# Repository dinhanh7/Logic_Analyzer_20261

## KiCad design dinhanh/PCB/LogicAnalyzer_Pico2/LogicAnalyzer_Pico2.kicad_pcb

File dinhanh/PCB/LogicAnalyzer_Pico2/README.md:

# PCB đế Pico 2 — Logic Analyzer 8 kênh, Layout A

**Rev A1 — 11/11/2026. Bản thiết kế để nhóm duyệt, chưa phát hành sản xuất.**

Đã vẽ schematic và PCB 2 lớp **160 × 110 mm**, đi dây, đổ đồng GND, bố trí 4 lỗ M3. Pico 2 đã hàn chân đực cắm vào **hai socket cái 1×20, bước 2,54 mm**, khoảng cách hai hàng **17,78 mm**. USB trên Pico quay ra mép trên; dùng USB này để cấp nguồn và giao tiếp PC.

Căn cứ: [spec](../SPEC_PCB.md), [phản hồi Nam Khánh](../REPLY_SPEC_PCB.md), [mạch bảo vệ LTspice](../../mach_bao_ve/ltspice/README.md). Không thay đổi source firmware hoặc file mô phỏng trong lần vẽ PCB này.

## Mở và duyệt

- Mở **[LogicAnalyzer_Pico2.kicad_pro](LogicAnalyzer_Pico2.kicad_pro)** trong KiCad 10, rồi mở Schematic Editor / PCB Editor.
- Schematic native: [LogicAnalyzer_Pico2.kicad_sch](LogicAnalyzer_Pico2.kicad_sch); PCB native: [LogicAnalyzer_Pico2.kicad_pcb](LogicAnalyzer_Pico2.kicad_pcb).
- [Schematic PDF](review/Schematic.pdf), [ảnh 3D mặt trên](review/PCB_3D_top.png), [ảnh 3D phối cảnh](review/PCB_3D_isometric.png).
- [Mặt trên SVG](review/PCB_top.svg), [mặt dưới SVG](review/PCB_bottom.svg), [bản đồ lắp linh kiện](review/Assembly.svg).
- [PDF mặt trên tỉ lệ 1:1](review/PCB_top_1to1.pdf), [PDF mặt dưới tỉ lệ 1:1](review/PCB_bottom_1to1.pdf): in **Actual size / 100%**, kiểm tra bằng thước trước khi đối chiếu socket.
- [BOM từng vị trí](BOM.csv), [BOM gộp và phần mua ngoài bo](BOM_grouped.csv).
- [Gerber + drill để duyệt](fabrication_review/). Các file này chưa được nhóm xác nhận để đặt làm bo.

Symbol, footprint và model cần dùng được kèm trong project bằng đường dẫn `${KIPRJMOD}`. Không cần thư viện riêng đã bị xóa ở `mach_bao_ve/kicad/`. Xem [nguồn thư viện](LIBRARY_SOURCES.md). Model PR02 là hình minh họa theo kích thước danh định; model Pico đi kèm thư viện KiCad minh họa cơ khí dòng Pico, không thể hiện chính xác linh kiện RP2350 trên Pico 2. Chưa dựng model TFT/hộp vì chưa có mã module và cơ khí thực tế.

## Chức năng và kết nối

### Tám kênh bảo vệ

Mỗi kênh có đường tín hiệu:

```text
J1 CHn → 1k PR02 → 1k PR02 → CLAMP_n → 330Ω → A_n → SN74LVC1G17 → 33Ω → GPn
                                                       │
                                                      47k
                                                       │
                                                      GND

BAV99: pin 1 = GND; pin 2 = Z_n; pin 3 = CLAMP_n
BZX85C3V3: cathode = Z_n; anode = GND
```

Tổng cộng **16 điện trở PR02 Cu-lead 1 kΩ/2 W**. Mã đề xuất theo cấu trúc mã Vishay là **PR02000201001FA100** (1%); cần đối chiếu mã đặt mua thực tế, không thay bằng PR02 FeCu công suất khác hoặc điện trở SMD thông thường. Footprint riêng: thân tối đa 10 × Ø3,9 mm, khoảng cách chân 17,78 mm, lỗ khoan 1,2 mm. Chừa khoảng trống giữa các thân điện trở; các điện trở/tụ tín hiệu còn lại dùng 0805 để dễ hàn tay, tụ khối dùng 1206.

**Z_n là nút kẹp riêng từng kênh, không nối rail 3V3.** Chỉ ngõ Y của buffer qua điện trở 33 Ω tới Pico. Test point gồm OUT0…OUT7, 3V3, VSYS, GND; CH0 có thêm IN/CLAMP/A/Z. TP là pad đồng trên bo, không phải linh kiện phải mua.

Đồng GND mặt dưới nằm từ x = 65 mm sang vùng bảo vệ/Pico/giao diện; không trải dưới phần lớn vùng điện trở đầu vào. Có đường GND riêng rộng 0,8 mm vòng dưới vùng điện trở nối về đầu probe. Đây là thiết bị **chung GND với DUT/PC**, không cách ly.

### Đầu nối

| Đầu nối | Pin | Chức năng |
|---|---|---|
| J1 — 2×8 | 1,3,5,7,9,11,13,15 | CH0…CH7 |
| J1 — 2×8 | 2,4,6,8,10,12,14,16 | GND |
| J2 — 1×8 | 1 / 2 | GND / 3V3 |
| J2 | 3 / 4 | TFT SCK GP10 / MOSI GP11 |
| J2 | 5 / 6 | TFT RST GP15 / DC GP14 |
| J2 | 7 / 8 | TFT CS GP13 / BL sau tầng lái GP16 |
| J3 — 1×2 | 1 / 2 | CAL_OUT GP27 / GND |

**J2 là đầu cáp được gán tín hiệu rõ ràng, chưa phải đầu cắm trực tiếp tương thích mọi module ST7735.** Phải nối dây theo nhãn của module thật. Chưa đặt lỗ bắt vít cố định cho TFT; dùng gá/hộp riêng sau khi đo module.

### Nút, LED, nguồn

| Vị trí | Chức năng | Pico |
|---|---|---|
| SW1 / SW2 | UP / DOWN, nhấn nối GND | GP8 / GP9 |
| SW3 / SW4 | OK / BACK, nhấn nối GND | GP12 / GP22 |
| SW5 | RESET, nhấn nối GND | RUN |
| D17 | PWR từ 3V3 qua 1 kΩ | — |
| D18 | STATUS qua 1 kΩ, HIGH sáng | GP26 |
| J3 | Xung tự kiểm tra 3,3 V | GP27 |

Các nút chức năng dùng pull-up nội và debounce firmware; RUN đã có pull-up trên module. GP17…GP21 và GP28 để trống. CAL_OUT không nối sẵn vào đầu đo; nối bằng dây khi kiểm tra và không dùng để cấp nguồn DUT.

Nguồn duy nhất là USB trên Pico; rail 3V3 từ pin 36 cấp buffer, TFT, BL và LED. VSYS chỉ đưa ra TP10. Có C9/C10 10 µF/10 V và 100 nF cạnh mỗi buffer. Chưa đo tổng dòng; yêu cầu tải ngoài nằm trong ngân sách nguồn Pico, mục tiêu dưới 300 mA. Kiểm tra dòng module TFT, BL và sụt áp thực tế trước khi duyệt.

### Tầng lái BL bổ sung

Q1 BC817-40 và Q2 BC807-40 tạo công tắc cấp 3,3 V cho BL, **GP16 HIGH → sáng**, giữ logic Layout A. GPIO chỉ cấp dòng base khoảng 0,5 mA, không trực tiếp cấp dòng LED nền. Có điện trở kéo để BL tắt khi GPIO ở trạng thái thả nổi.

R47 mặc định **100 Ω, 0805, chọn công suất ≥0,25 W** để giới hạn dòng tối đa lý thuyết 33 mA nếu đầu BL chập GND. Với module có điện trở hoặc mạch BL riêng, độ sáng có thể thấp. Chỉ thay trị số sau khi biết cấu trúc BL và dòng thực tế; không tự lắp 0 Ω trước khi kiểm tra. Tầng này dùng với đầu BL nhận mức/dòng dương 3,3 V; nếu module có BL kiểu khác phải sửa trước khi cắm.

## Kết quả kiểm tra bản vẽ

KiCad **10.0.8**:

| Kiểm tra | Kết quả |
|---|---:|
| [ERC schematic](review/ERC.json) | 0 lỗi, 0 cảnh báo |
| [DRC PCB, gồm đối chiếu schematic](review/DRC.json) | 0 vi phạm |
| Kết nối PCB còn thiếu | 0 |
| Sai khác PCB với schematic | 0 |
| [Kiểm tra topology/pinout riêng](review/connectivity_check.json) | 84 kiểm tra đạt |

Không thêm ngoại lệ DRC để bỏ qua lỗi. Quy tắc bo: clearance tín hiệu mặc định 0,22 mm; net trước hai điện trở đầu vào 0,75 mm; rộng dây nhỏ nhất 0,20 mm, danh định 0,25 mm; via tối thiểu 0,60/0,30 mm; cách mép đồng 0,50 mm. Các trị số này là lựa chọn layout prototype, không phải chứng nhận cách điện hay mức đo CAT.

Đã dùng đường đi ngắn trong từng front-end; dây buffer→Pico có chiều dài khác nhau, chưa cân bằng timing bằng đo thực nghiệm. Kiểm tra 84 điều kiện dùng netlist xuất thật để xác nhận pin probe, hai điện trở nối tiếp, các nút Z riêng, mapping Layout A và việc không nối nút trước buffer vào chân capture.

Đi dây phần còn lại bằng **Freerouting 2.5.0 chạy cục bộ**, sau đó sửa copper bằng KiCad và kiểm tra lại DRC. Không gửi thiết kế lên dịch vụ route đám mây. File DSN/SES được giữ trong `review/` để truy vết; **PCB native hiện tại đã có chỉnh sửa sau SES**, nên không import lại SES lên bản này.

## Những điểm cần nhóm chốt trước khi đặt làm

1. **Đối chiếu Pico/socket thật:** in PDF 1:1, thử khoảng cách chân và chiều cắm, chiều cao socket, USB/BOOTSEL/SWD. Không cắm ngược Pico. Lỗ H1…H4 là Ø3,2 mm tại (4;4), (156;4), (4;106), (156;106) mm, tính từ góc trên trái.
2. **Module TFT thật:** thứ tự chân, nguồn 3,3 V, cấu trúc/dòng BL, dây nối J2 và chỗ gá màn hình. Không cấp 5 V lên J2.
3. **Linh kiện bảo vệ:** xác nhận mã PR02 Cu, đường cong chịu xung/điện áp, mã BAV99/BZX85C3V3/SN74LVC1G17DBVR và package. Kiểm tra điện áp chịu được của đầu nối/dây probe được mua. Trị số 2×1 kΩ trên PCB khớp tổng R=2 kΩ của mô hình cũ, nhưng hồ sơ LTspice vẫn cần cập nhật thành hai linh kiện và xét dung sai/ký sinh.
4. **Điện và timing:** kiểm thử 0/3,3 V trước, mapping từng kênh, dòng nguồn, TFT/nút/BL; đánh giá +12 V DC và mô phỏng xung +200 V/1 ms với linh kiện thực tế; xác minh dải 1 kHz–1 MHz và lệch thời gian giữa kênh. **25 MS/s không có nghĩa băng thông đầu vào 25 MHz. ERC/DRC không chứng minh chịu quá áp.**
5. **Cơ khí và chi phí:** duyệt kích thước 160×110 mm, cách gá TFT/hộp, báo giá PCB/linh kiện và mục tiêu ≤450.000 đ. Chưa có báo giá để xác nhận đạt ngân sách.

## Script và tái tạo

Các script nằm trong `scripts/`; đây là công cụ tạo bản ban đầu, **chạy lại có thể ghi đè sửa tay**. Hai file native hiện tại là kết quả bàn giao chính.

Thứ tự dựng lại: `generate_schematic.py` (Python có `sexpdata`) → KiCad CLI xuất `review/netlist.xml` → `generate_board.py` (Python có `pcbnew`) → Freerouting xuất `review/routed.ses` → `finish_board.py` → `refine_board.py` → `add_preview_models.py` → chạy lại ERC/DRC và `verify_connectivity.py`. Phải xuất lại PDF/Gerber sau mỗi thay đổi.

`generate_board.py` tạo phần bố trí và dây cục bộ, không tự tái tạo phần route từ Freerouting. KiCad đang cài qua AppDir có thể chạy các script PCB bằng `AppRun python3.11 <script>`. Các file native mở bằng KiCad không cần Python hay Freerouting.

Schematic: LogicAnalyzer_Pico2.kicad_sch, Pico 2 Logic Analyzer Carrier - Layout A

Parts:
C1, C2, C3, C4, C5, C6, C7, C8: 100n 10V; C0805
C9, C10: 10u / 10V X7R; C1206
D1, D3, D5, D7, D9, D11, D13, D15: BAV99; SOT23
D2, D4, D6, D8, D10, D12, D14, D16: BZX85C3V3; Zener_DO41
D17: PWR; LED0805
D18: STATUS; LED0805
H1, H2, H3, H4: M3 / 3.2mm; Hole_M3
J1: PROBE CH0..7 / GND; Probe_2x08
J2: TFT CABLE / 3V3 ONLY; TFT_1x08
J3: CAL OUT / GND; CAL_1x02
Q1: BC817-40; SOT23
Q2: BC807-40; SOT23
R1, R2, R6, R7, R11, R12, R16, R17, R21, R22, R26, R27, R31, R32, R36, R37: 1k PR02 2W; PR02_1k_2W_P17.78
R3, R8, R13, R18, R23, R28, R33, R38: 330R; R0805
R4, R9, R14, R19, R24, R29, R34, R39, R44, R46: 47k; R0805
R5, R10, R15, R20, R25, R30, R35, R40: 33R; R0805
R41, R42: 1k; R0805
R43, R45: 4k7; R0805
R47: 100R; R0805
R48: 100k; R0805
SW1: UP; SW_6mm
SW2: DOWN; SW_6mm
SW3: OK; SW_6mm
SW4: BACK; SW_6mm
SW5: RESET; SW_6mm
TP1: OUT0; TP_1mm
TP2: OUT1; TP_1mm
TP3: OUT2; TP_1mm
TP4: OUT3; TP_1mm
TP5: OUT4; TP_1mm
TP6: OUT5; TP_1mm
TP7: OUT6; TP_1mm
TP8: OUT7; TP_1mm
TP9: +3V3; TP_1mm
TP10: VSYS; TP_1mm
TP11: GND; TP_1mm
TP12: IN0; TP_1mm
TP13: CLAMP_0; TP_1mm
TP14: A_0; TP_1mm
TP15: Z_0; TP_1mm
U1, U2, U3, U4, U5, U6, U7, U8: SN74LVC1G17DBVR; SOT23_5
U9: Pico 2 + 2x female 1x20; Pico2_Sockets

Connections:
/+3V3: C1.1, C2.1, C3.1, C4.1, C5.1, C6.1, C7.1, C8.1, C9.1, C10.1, J2.2, Q2.2 (E), R41.1, R46.2, TP9.1, U1.5 (VCC), U2.5 (VCC), U3.5 (VCC), U4.5 (VCC), U5.5 (VCC), U6.5 (VCC), U7.5 (VCC), U8.5 (VCC), U9.36 (3V3_OUT)
/A_0: R3.2, R4.1, TP14.1, U1.2
/A_1: R8.2, R9.1, U2.2
/A_2: R13.2, R14.1, U3.2
/A_3: R18.2, R19.1, U4.2
/A_4: R23.2, R24.1, U5.2
/A_5: R28.2, R29.1, U6.2
/A_6: R33.2, R34.1, U7.2
/A_7: R38.2, R39.1, U8.2
/BL_N_BASE: Q1.1 (B), R43.2, R44.1
/BL_N_COL: Q1.3 (C), R45.1
/BL_PWR: Q2.3 (C), R47.1
/BL_P_BASE: Q2.1 (B), R45.2, R46.1
/BTN_BACK: SW4.1, U9.29 (GP22)
/BTN_DOWN: SW2.1, U9.12 (GP9)
/BTN_OK: SW3.1, U9.16 (GP12)
/BTN_UP: SW1.1, U9.11 (GP8)
/CAL_OUT: J3.1, U9.32 (GP27)
/CLAMP_0: D1.3 (K1_A2), R2.2, R3.1, TP13.1
/CLAMP_1: D3.3 (K1_A2), R7.2, R8.1
/CLAMP_2: D5.3 (K1_A2), R12.2, R13.1
/CLAMP_3: D7.3 (K1_A2), R17.2, R18.1
/CLAMP_4: D9.3 (K1_A2), R22.2, R23.1
/CLAMP_5: D11.3 (K1_A2), R27.2, R28.1
/CLAMP_6: D13.3 (K1_A2), R32.2, R33.1
/CLAMP_7: D15.3 (K1_A2), R37.2, R38.1
/GND: C1.2, C2.2, C3.2, C4.2, C5.2, C6.2, C7.2, C8.2, C9.2, C10.2, D1.1 (A1), D2.2 (A), D3.1 (A1), D4.2 (A), D5.1 (A1), D6.2 (A), D7.1 (A1), D8.2 (A), D9.1 (A1), D10.2 (A), D11.1 (A1), D12.2 (A), D13.1 (A1), D14.2 (A), D15.1 (A1), D16.2 (A), D17.1 (K), D18.1 (K), J1.2, J1.4, J1.6, J1.8, J1.10, J1.12, J1.14, J1.16, J2.1, J3.2, Q1.2 (E), R4.2, R9.2, R14.2, R19.2, R24.2, R29.2, R34.2, R39.2, R44.2, R48.2, SW1.2, SW2.2, SW3.2, SW4.2, SW5.2, TP11.1, U1.3 (GND), U2.3 (GND), U3.3 (GND), U4.3 (GND), U5.3 (GND), U6.3 (GND), U7.3 (GND), U8.3 (GND), U9.3 (GND), U9.8 (GND), U9.13 (GND), U9.18 (GND), U9.23 (GND), U9.28 (GND), U9.33 (AGND), U9.38 (GND)
/IN0: J1.1, R1.1, TP12.1
/IN1: J1.3, R6.1
/IN2: J1.5, R11.1
/IN3: J1.7, R16.1
/IN4: J1.9, R21.1
/IN5: J1.11, R26.1
/IN6: J1.13, R31.1
/IN7: J1.15, R36.1
/LED0_A: D17.2 (A), R41.2
/LED1_A: D18.2 (A), R42.2
/LED_STATUS: R42.1, U9.31 (GP26)
/MID_0: R1.2, R2.1
/MID_1: R6.2, R7.1
/MID_2: R11.2, R12.1
/MID_3: R16.2, R17.1
/MID_4: R21.2, R22.1
/MID_5: R26.2, R27.1
/MID_6: R31.2, R32.1
/MID_7: R36.2, R37.1
/OUT0: R5.2, TP1.1, U9.1 (GP0)
/OUT1: R10.2, TP2.1, U9.2 (GP1)
/OUT2: R15.2, TP3.1, U9.4 (GP2)
/OUT3: R20.2, TP4.1, U9.5 (GP3)
/OUT4: R25.2, TP5.1, U9.6 (GP4)
/OUT5: R30.2, TP6.1, U9.7 (GP5)
/OUT6: R35.2, TP7.1, U9.9 (GP6)
/OUT7: R40.2, TP8.1, U9.10 (GP7)
/RUN: SW5.1, U9.30 (RUN)
/TFT_BL: J2.8, R47.2, R48.1
/TFT_BL_CTRL: R43.1, U9.21 (GP16)
/TFT_CS: J2.7, U9.17 (GP13)
/TFT_DC: J2.6, U9.19 (GP14)
/TFT_MOSI: J2.4, U9.15 (GP11)
/TFT_RST: J2.5, U9.20 (GP15)
/TFT_SCK: J2.3, U9.14 (GP10)
/VSYS: TP10.1, U9.39 (VSYS)
/Y_0: R5.1, U1.4
/Y_1: R10.1, U2.4
/Y_2: R15.1, U3.4
/Y_3: R20.1, U4.4
/Y_4: R25.1, U5.4
/Y_5: R30.1, U6.4
/Y_6: R35.1, U7.4
/Y_7: R40.1, U8.4
/Z_0: D1.2 (K2), D2.1 (K), TP15.1
/Z_1: D3.2 (K2), D4.1 (K)
/Z_2: D5.2 (K2), D6.1 (K)
/Z_3: D7.2 (K2), D8.1 (K)
/Z_4: D9.2 (K2), D10.1 (K)
/Z_5: D11.2 (K2), D12.1 (K)
/Z_6: D13.2 (K2), D14.1 (K)
/Z_7: D15.2 (K2), D16.1 (K)

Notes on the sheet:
LOGIC ANALYZER - PICO 2 CARRIER / LAYOUT A
Rev A1 | 8 channels | 25 MS/s capture | USB-only | ST7735 SPI1 | engineering review
PICO MODULE / FEMALE SOCKETS
USB power/data through Pico only. No external VSYS supply. GP17..GP21, GP28 unconnected. Keep BOOTSEL / module SWD accessible.
ODD: CH0..7 EVEN: GND Common ground; no isolation.
1 GND 2 3V3 3 SCK 4 MOSI 5 RST 6 DC 7 CS 8 BL Cable adapter to actual ST7735 module.
Buttons: internal Pico pull-ups + firmware debounce. RESET shorts RUN to GND; pull-up already on Pico.
CAL = GP27; connect to input with an external wire.
TFT BACKLIGHT - ACTIVE HIGH, DEFAULT 100R LIMIT
Default BL series 100R limits current <=33mA; can dim some modules. Change only after checking module BL circuit/current. GP16 HIGH = ON. Do not connect raw backlight LED to GP16.
CH0 PULSE LIMITER / CLAMP TO GND / SCHMITT BUFFER
Target +12V continuous / +200V single 1ms; validate with exact parts + parasitics.
CH1 PULSE LIMITER / CLAMP TO GND / SCHMITT BUFFER
CH2 PULSE LIMITER / CLAMP TO GND / SCHMITT BUFFER
CH3 PULSE LIMITER / CLAMP TO GND / SCHMITT BUFFER
CH4 PULSE LIMITER / CLAMP TO GND / SCHMITT BUFFER
CH5 PULSE LIMITER / CLAMP TO GND / SCHMITT BUFFER
CH6 PULSE LIMITER / CLAMP TO GND / SCHMITT BUFFER
CH7 PULSE LIMITER / CLAMP TO GND / SCHMITT BUFFER
ASSEMBLY / VALIDATION NOTES
Two-layer carrier, 160 x 110 mm. Pico 2 plugs into 2x20 female sockets. TFT uses labeled cable connector J2. No unverified direct-mating TFT footprint. All eight Z nodes are independent. Never connect Z/CLAMP to +3V3. GP0..7 connect only to buffer Y via 33R. 3V3 load target below 300mA; measure Pic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

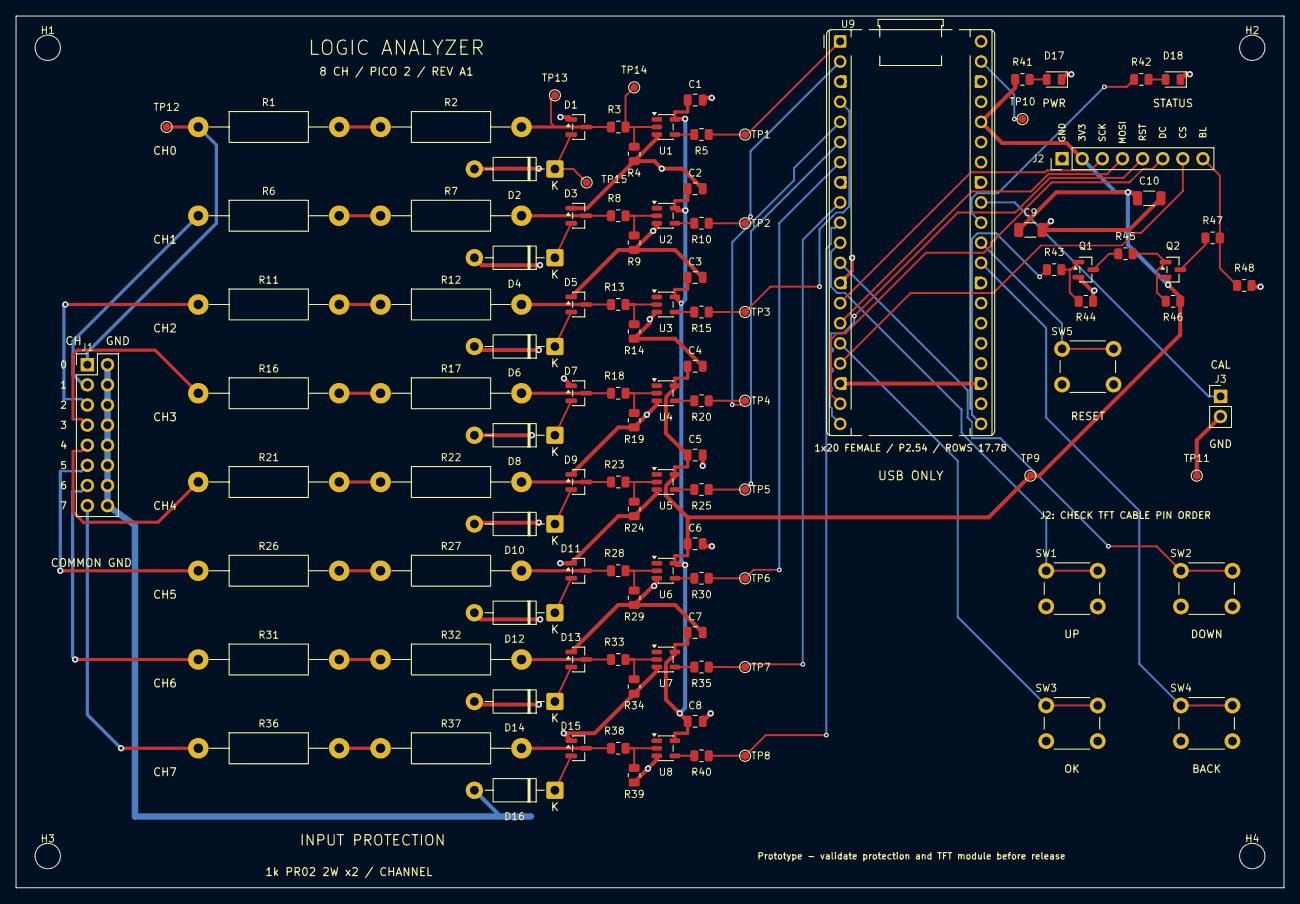
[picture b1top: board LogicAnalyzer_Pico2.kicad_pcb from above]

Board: 2 copper layers, 160.0 x 110.0 mm, 114 parts (0 on the bottom side), 79 nets.

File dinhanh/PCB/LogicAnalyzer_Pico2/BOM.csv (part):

Reference,Value,Footprint,Datasheet,Note
U9,Pico 2 + 2x female 1x20,LogicAnalyzer:Pico2_Sockets,https://datasheets.raspberrypi.com/pico/pico-2-datasheet.pdf,"Fit two female 1x20 2.54mm sockets, row spacing 17.78mm; USB and regulator are on the plug-in Pico 2."
J1,PROBE CH0..7 / GND,LogicAnalyzer:Probe_2x08,,
J2,TFT CABLE / 3V3 ONLY,LogicAnalyzer:TFT_1x08,,Generic labeled cable header. Verify actual TFT pin order before wiring. No MISO.
SW1,UP,LogicAnalyzer:SW_6mm,,
SW2,DOWN,LogicAnalyzer:SW_6mm,,
SW3,OK,LogicAnalyzer:SW_6mm,,
SW4,BACK,LogicAnalyzer:SW_6mm,,
SW5,RESET,LogicAnalyzer:SW_6mm,,
C9,10u / 10V X7R,LogicAnalyzer:C1206,,"Bulk, effective capacitance at 3.3V to be checked."
C10,10u / 10V X7R,LogicAnalyzer:C1206,,Near TFT header.
R41,1k,LogicAnalyzer:R0805,,
D17,PWR,LogicAnalyzer:LED0805,,
R42,1k,LogicAnalyzer:R0805,,
D18,STATUS,LogicAnalyzer:LED0805,,
J3,CAL OUT / GND,LogicAnalyzer:CAL_1x02,,
Q1,BC817-40,LogicAnalyzer:SOT23,,"B=1 E=2 C=3; drives high-side PNP only, not backlight current directly."
R43,4k7,LogicAnalyzer:R0805,,
R44,47k,LogicAnalyzer:R0805,,
Q2,BC807-40,LogicAnalyzer:SOT23,,B=1 E=2 C=3; high-side backlight power. Module must tolerate 3.3V BL.
R45,4k7,LogicAnalyzer:R0805,,
R46,47k,LogicAnalyzer:R0805,,
R47,100R,LogicAnalyzer:R0805,,
R48,100k,LogicAnalyzer:R0805,,
TP9,+3V3,LogicAnalyzer:TP_1mm,,
TP10,VSYS,LogicAnalyzer:TP_1mm,,
TP11,GND,LogicAnalyzer:TP_1mm,,
TP12,IN0,LogicAnalyzer:TP_1mm,,
TP13,CLAMP_0,LogicAnalyzer:TP_1mm,,
TP14,A_0,LogicAnalyzer:TP_1mm,,
TP15,Z_0,LogicAnalyzer:TP_1mm,,
R1,1k PR02 2W,LogicAnalyzer:PR02_1k_2W_P17.78,https://www.vishay.com/docs/28729/pr010203.pdf,"Cu-lead PR02, 1%, proposed order code PR02000201001FA100; validate pulse curve. Do not replace with ordinary SMD resistor."
R2,1k PR02 2W,LogicAnalyzer:PR02_1k_2W_P17.78,https://www.vishay.com/docs/28729/pr010203.pdf,"Cu-lead PR02, 1%, proposed order code PR02000201001FA100; validate pulse curve. Do not replace with ordinary SMD resistor."
R3,330R,LogicAnalyzer:R0805,,
R4,47k,LogicAnalyzer:R0805,,
D1,BAV99,LogicAnalyzer:SOT23,https://assets.nexperia.com/documents/data-sheet/BAV99.pdf,"1=GND (A1), 2=Z (K2), 3=CLAMP (K1/A2). Z is private to this channel, NOT +3V3."
D2,BZX85C3V3,LogicAnalyzer:Zener_DO41,https://www.vishay.com/docs/85607/bzx85.pdf,
U1,SN74LVC1G17DBVR,LogicAnalyzer:SOT23_5,https://www.ti.com/lit/ds/symlink/sn74lvc1g17.pdf,DBV 1=NC 2=A 3=GND 4=Y 5=VCC. Only Y ->33R connects to Pico.
R5,33R,LogicAnalyzer:R0805,,
C1,100n 10V,LogicAnalyzer:C0805,,
TP1,OUT0,LogicAnalyzer:TP_1mm,,
R6,1k PR02 2W,LogicAnalyzer:PR02_1k_2W_P17.78,https://www.vishay.com/docs/28729/pr010203.pdf,"Cu-lead PR02, 1%, proposed order code PR02000201001FA100; validate pulse curve. Do not replace with ordinary SMD resistor."
R7,1k PR02 2W,LogicAnalyzer:PR02_1k_2W_P17.78,https://www.vishay.com/docs/28729/pr010203.pdf,"Cu-lead PR02, 1%, proposed order code PR02000201001FA100; validate pulse curve. Do not replace with ordinary SMD resistor."
R8,330R,LogicAnalyzer:R0805,,
R9,47k,LogicAnalyzer:R0805,,
D3,BAV99,LogicAnalyzer:SOT23,https://assets.nexperia.com/documents/data-sheet/BAV99.pdf,"1=GND (A1), 2=Z (K2), 3=CLAMP (K1/A2). Z is private to this channel, NOT +3V3."
D4,BZX85C3V3,LogicAnalyzer:Zener_DO41,https://www.vishay.com/docs/85607/bzx85.pdf,
U2,SN74LVC1G17DBVR,LogicAnalyzer:SOT23_5,https://www.ti.com/lit/ds/symlink/sn74lvc1g17.pdf,DBV 1=NC 2=A 3=GND 4=Y 5=VCC. Only Y ->33R connects to Pico.
R10,33R,LogicAnalyzer:R0805,,
C2,100n 10V,LogicAnalyzer:C0805,,
TP2,OUT1,LogicAnalyzer:TP_1mm,,
R11,1k PR02 2W,LogicAnalyzer:PR02_1k_2W_P17.78,https://www.vishay.com/docs/28729/pr010203.pdf,"Cu-lead PR02, 1%, proposed order code PR02000201001FA100; validate pulse curve. Do not replace with ordinary SMD resistor."
R12,1k PR02 2W,LogicAnalyzer:PR02_1k_2W_P17.78,https://www.vishay.com/docs/28729/pr010203.pdf,"Cu-lead PR02, 1%, proposed order code PR02000201001FA100; validate pulse curve. Do not replace with ordinary SMD resistor."
R13,330R,LogicAnalyzer:R0805,,
R14,47k,LogicAnalyzer:R0805,,
D5,BAV99,LogicAnalyzer:SOT23,https://assets.nexperia.com/documents/data-sheet/BAV99.pdf,"1=GND (A1), 2=Z (K2), 3=CLAMP (K1/A2). Z is private to this channel, NOT +3V3."
D6,BZX85C3V3,LogicAnalyzer:Zener_DO41,https://www.vishay.com/docs/85607/bzx85.pdf,
U3,SN74LVC1G17DBVR,LogicAnalyzer:SOT23_5,https://www.ti.com/lit/ds/symlink/sn74lvc1g17.pdf,DBV 1=NC 2=A 3=GND 4=Y 5=VCC. Only Y ->33R connects to Pico.
R15,33R,LogicAnalyzer:R0805,,
C3,100n 10V,LogicAnalyzer:C0805,,
TP3,OUT2,LogicAnalyzer:TP_1mm,,
R16,1k PR02 2W,LogicAnalyzer:PR02_1k_2W_P17.78,https://www.vishay.com/docs/28729/pr010203.pdf,"Cu-lead PR02, 1%, proposed order code PR02000201001FA100; validate pulse curve. Do not replace with ordinary SMD resistor."
R17,1k PR02 2W,LogicAnalyzer:PR02_1k_2W_P17.78,https://www.vishay.com/docs/28729/pr010203.pdf,"Cu-lead PR02, 1%, proposed order code PR02000201001FA100; validate pulse curve. Do not replace with ordinary SMD resistor."
R18,330R,LogicAnalyzer:R0805,,
R19,47k,LogicAnalyzer:R0805,,
D7,BAV99,LogicAnalyzer:SOT23,https://assets.nexperia.com/documents/data-sheet/BAV99.pdf,"1=GND (A1), 2=Z (K2), 3=CLAMP (K1/A2). Z is private to this channel, NOT +3V3."
D8,BZX85C3V3,LogicAnalyzer:Zener_DO41,https://www.vishay.com/docs/85607/bzx85.pdf,
U4,SN74LVC1G17DBVR,LogicAnalyzer:SOT23_5,https://www.ti.com/lit/ds/symlink/sn74lvc1g17.pdf,DBV 1=NC 2=A 3=GND 4=Y 5=VCC. Only Y ->33R connects to Pico.
R20,33R,LogicAnalyzer:R0805,,
C4,100n 10V,LogicAnalyzer:C0805,,
TP4,OUT3,LogicAnalyzer:TP_1mm,,
R21,1k PR02 2W,LogicAnalyzer:PR02_1k_2W_P17.78,https://www.vishay.com/docs/28729/pr010203.pdf,"Cu-lead PR02, 1%, proposed order code PR02000201001FA100; validate pulse curve. Do not replace with ordinary SMD resistor."
R22,1k PR02 2W,LogicAnalyzer:PR02_1k_2W_P17.78,https://www.vishay.com/docs/28729/pr010203.pdf,"Cu-lead PR02, 1%, proposed order code PR02000201001FA100; validate pulse curve. Do not replace with ordinary SMD resistor."
R23,330R,LogicAnalyzer:R0805,,
R24,47k,LogicAnalyzer:R0805,,
D9,BAV99,LogicAnalyzer:SOT23,https://assets.nexperia.com/documents/data-sheet/BAV99.pdf,"1=GND (A1), 2=Z (K2), 3=CLAMP (K1/A2). Z is private to this channel, NOT +3V3."
D10,BZX85C3V3,LogicAnalyzer:Zener_DO41,https://www.vishay.com/docs/85607/bzx85.pdf,
U5,SN74LVC1G17DBVR,LogicAnalyzer:SOT23_5,https://www.ti.com/lit/ds/symlink/sn74lvc1g17.pdf,DBV 1=NC 2=A 3=GND 4=Y 5=VCC. Only Y ->33R connects to Pico.
R25,33R,LogicAnalyzer:R0805,,
C5,100n 10V,LogicAnalyzer:C0805,,
TP5,OUT4,LogicAnalyzer:TP_1mm,,
R26,1k PR02 2W,LogicAnalyzer:PR02_1k_2W_P17.78,https://www.vishay.com/docs/28729/pr010203.pdf,"Cu-lead PR02, 1%, proposed order code PR02000201001FA100; validate pulse curve. Do not replace with ordinary SMD resistor."
R27,1k PR02 2W,LogicAnalyzer:PR02_1k_2W_P17.78,https://www.vishay.com/docs/28729/pr010203.pdf,"Cu-lead PR02, 1%, proposed order code PR02000201001FA100; validate pulse curve. Do not replace with ordinary SMD resistor."
R28,330R,LogicAnalyzer:R0805,,
R29,47k,LogicAnalyzer:R0805,,
D11,BAV99,LogicAnalyzer:SOT23,https://assets.nexperia.com/documents/data-sheet/BAV99.pdf,"1=GND (A1), 2=Z (K2), 3=CLAMP (K1/A2). Z is private to this channel, NOT +3V3."
D12,BZX85C3V3,LogicAnalyzer:Zener_DO41,https://www.vishay.com/docs/85607/bzx85.pdf,
U6,SN74LVC1G17DBVR,LogicAnalyzer:SOT23_5,https://www.ti.com/lit/ds/symlink/sn74lvc1g17.pdf,DBV 1=NC 2=A 3=GND 4=Y 5=VCC. Only Y ->33R connects to Pico.
R30,33R,LogicAnalyzer:R0805,,
C6,100n 10V,LogicAnalyzer:C0805,,
TP6,OUT5,LogicAnalyzer:TP_1mm,,
R31,1k PR02 2W,LogicAnalyzer:PR02_1k_2W_P17.78,https://www.vishay.com/docs/28729/pr010203.pdf,"Cu-lead PR02, 1%, proposed order code PR02000201001FA100; validate pulse curve. Do not replace with ordinary SMD resistor."
R32,1k PR02 2W,LogicAnalyzer:PR02_1k_2W_P17.78,https://www.vishay.com/docs/28729/pr010203.pdf,"Cu-lead PR02, 1%, proposed order code PR02000201001FA100; validate pulse curve. Do not replace with ordinary SMD resistor."
R33,330R,LogicAnalyzer:R0805,,
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
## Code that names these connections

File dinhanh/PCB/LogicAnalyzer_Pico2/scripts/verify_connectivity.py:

#!/usr/bin/env python3
"""Check exported electrical topology independently of the drawing generator."""
import json,xml.etree.ElementTree as ET
from pathlib import Path
HERE=Path(__file__).resolve().parent.parent
root=ET.parse(HERE/'review/netlist.xml');nets={};by_pin={}
for net in root.findall('.//nets/net'):
 name=net.attrib['name'].lstrip('/');nodes={(n.attrib['ref'],n.attrib['pin']) for n in net.findall('node')};nets[name]=nodes
 for node in nodes:by_pin[node]=name
checks=[]
def check(ok,desc):
 if not ok:raise AssertionError(desc)
 checks.append(desc)
pico_capture=[1,2,4,5,6,7,9,10]
for i,pin in enumerate(pico_capture):
 r=lambda n:(f'R{5*i+n}', '1')
 check(by_pin[(f'U{i+1}','4')]==by_pin[(f'R{5*i+5}','1')],f'CH{i}: buffer Y reaches 33R input')
 check(by_pin[(f'R{5*i+5}','2')]==by_pin[('U9',str(pin))],f'CH{i}: only protected output reaches correct capture GPIO')
 check(nets[f'Z_{i}']=={(f'D{2*i+1}','2'),(f'D{2*i+2}','1')}|({('TP15','1')} if i==0 else set()),f'CH{i}: Zener cathode node private, never supply')
 check(by_pin[(f'D{2*i+1}','1')]=='GND' and by_pin[(f'D{2*i+2}','2')]=='GND',f'CH{i}: clamp current returns to GND')
 check(by_pin[('J1',str(2*i+1))]==by_pin[(f'R{5*i+1}','1')],f'CH{i}: probe pin odd is input')
 check(by_pin[('J1',str(2*i+2))]=='GND',f'CH{i}: probe pin even is ground')
 check(by_pin[(f'R{5*i+1}','2')]==by_pin[(f'R{5*i+2}','1')],f'CH{i}: two series resistors present')
 check(by_pin[(f'R{5*i+2}','2')]==by_pin[(f'D{2*i+1}','3')]==by_pin[(f'R{5*i+3}','1')],f'CH{i}: input clamp precedes 330R and buffer')
for pin,name in {11:'BTN_UP',12:'BTN_DOWN',16:'BTN_OK',29:'BTN_BACK',14:'TFT_SCK',15:'TFT_MOSI',17:'TFT_CS',19:'TFT_DC',20:'TFT_RST',21:'TFT_BL_CTRL',31:'LED_STATUS',32:'CAL_OUT'}.items():check(by_pin['U9',str(pin)]==name,f'Layout A: Pico pin {pin} = {name}')
for pin in (22,24,25,26,27,34):check(by_pin['U9',str(pin)].startswith('unconnected-'),f'Unused Pico pin {pin} remains unconnected')
check(all(r not in ('J1',) and not (r=='U9' and int(n) in pico_capture) for r,n in nets['+3V3']),'No raw input/capture GPIO tied to supply')
check(not any(r=='U9' and int(n) in pico_capture for k,v in nets.items() if k.startswith(('IN','MID_','CLAMP_','A_','Z_')) for r,n in v),'No high-energy/clamp node bypasses the buffer into Pico')
result={'status':'PASS','checks_passed':len(checks),'checks':checks}
(HERE/'review/connectivity_check.json').write_text(json.dumps(result,indent=2)+'\n')
print(f'PASS: {len(checks)} topology / pin-mapping checks.')
